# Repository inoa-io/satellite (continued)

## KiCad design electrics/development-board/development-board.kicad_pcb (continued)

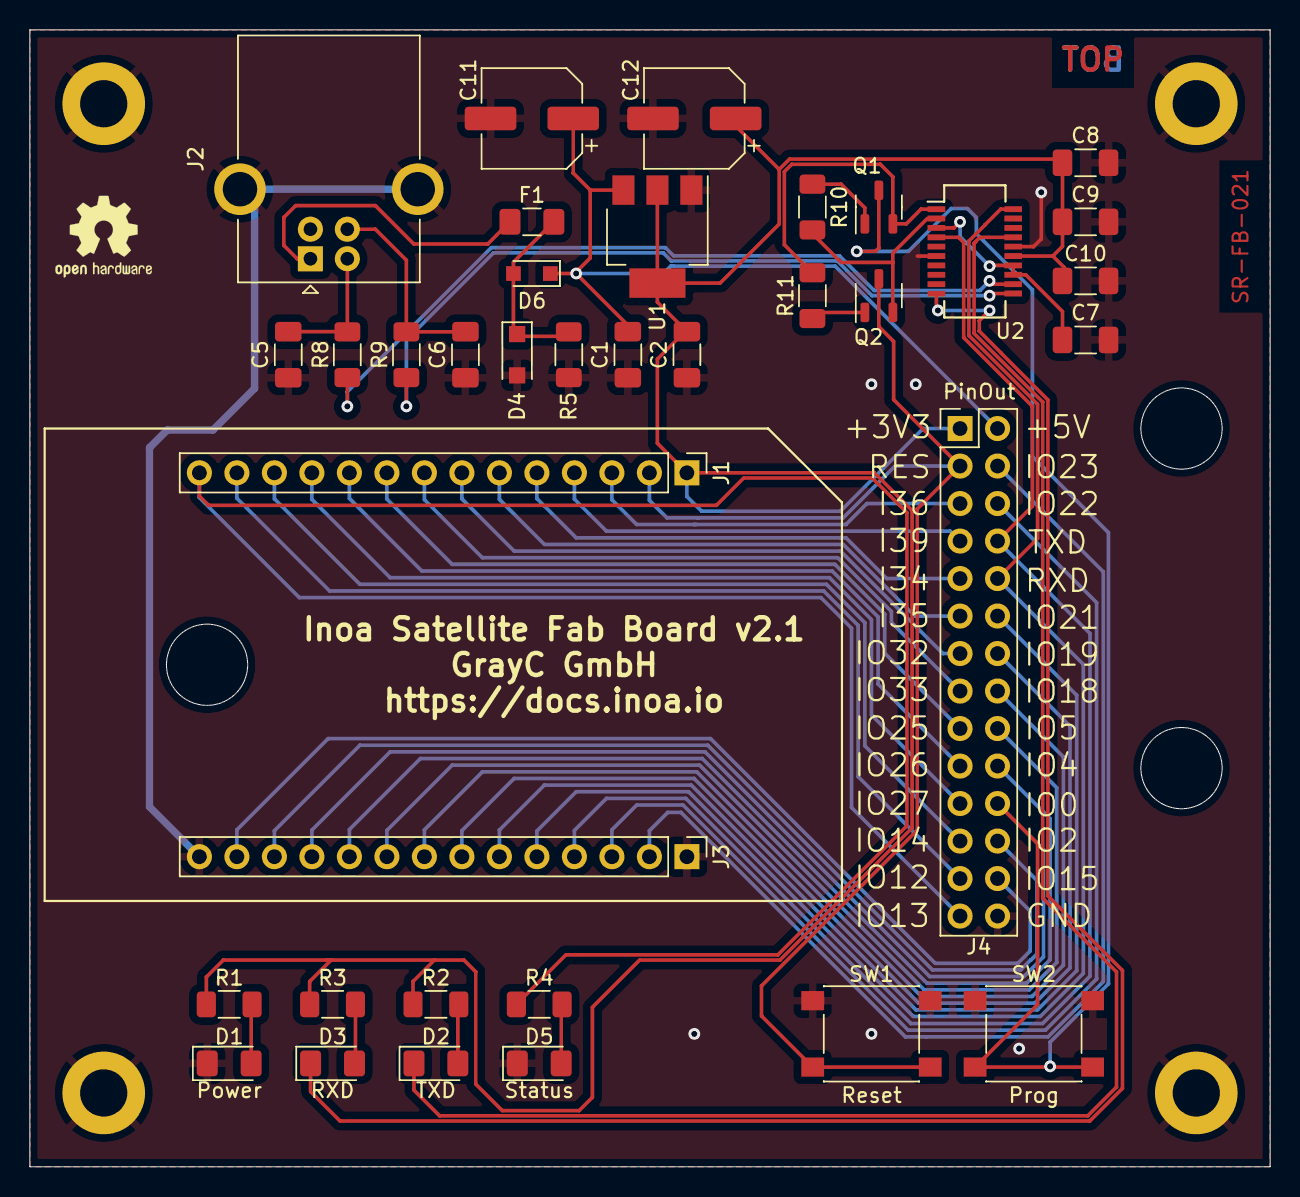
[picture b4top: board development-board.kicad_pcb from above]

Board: 2 copper layers, 84.0 x 77.0 mm, 45 parts (0 on the bottom side), 45 nets.

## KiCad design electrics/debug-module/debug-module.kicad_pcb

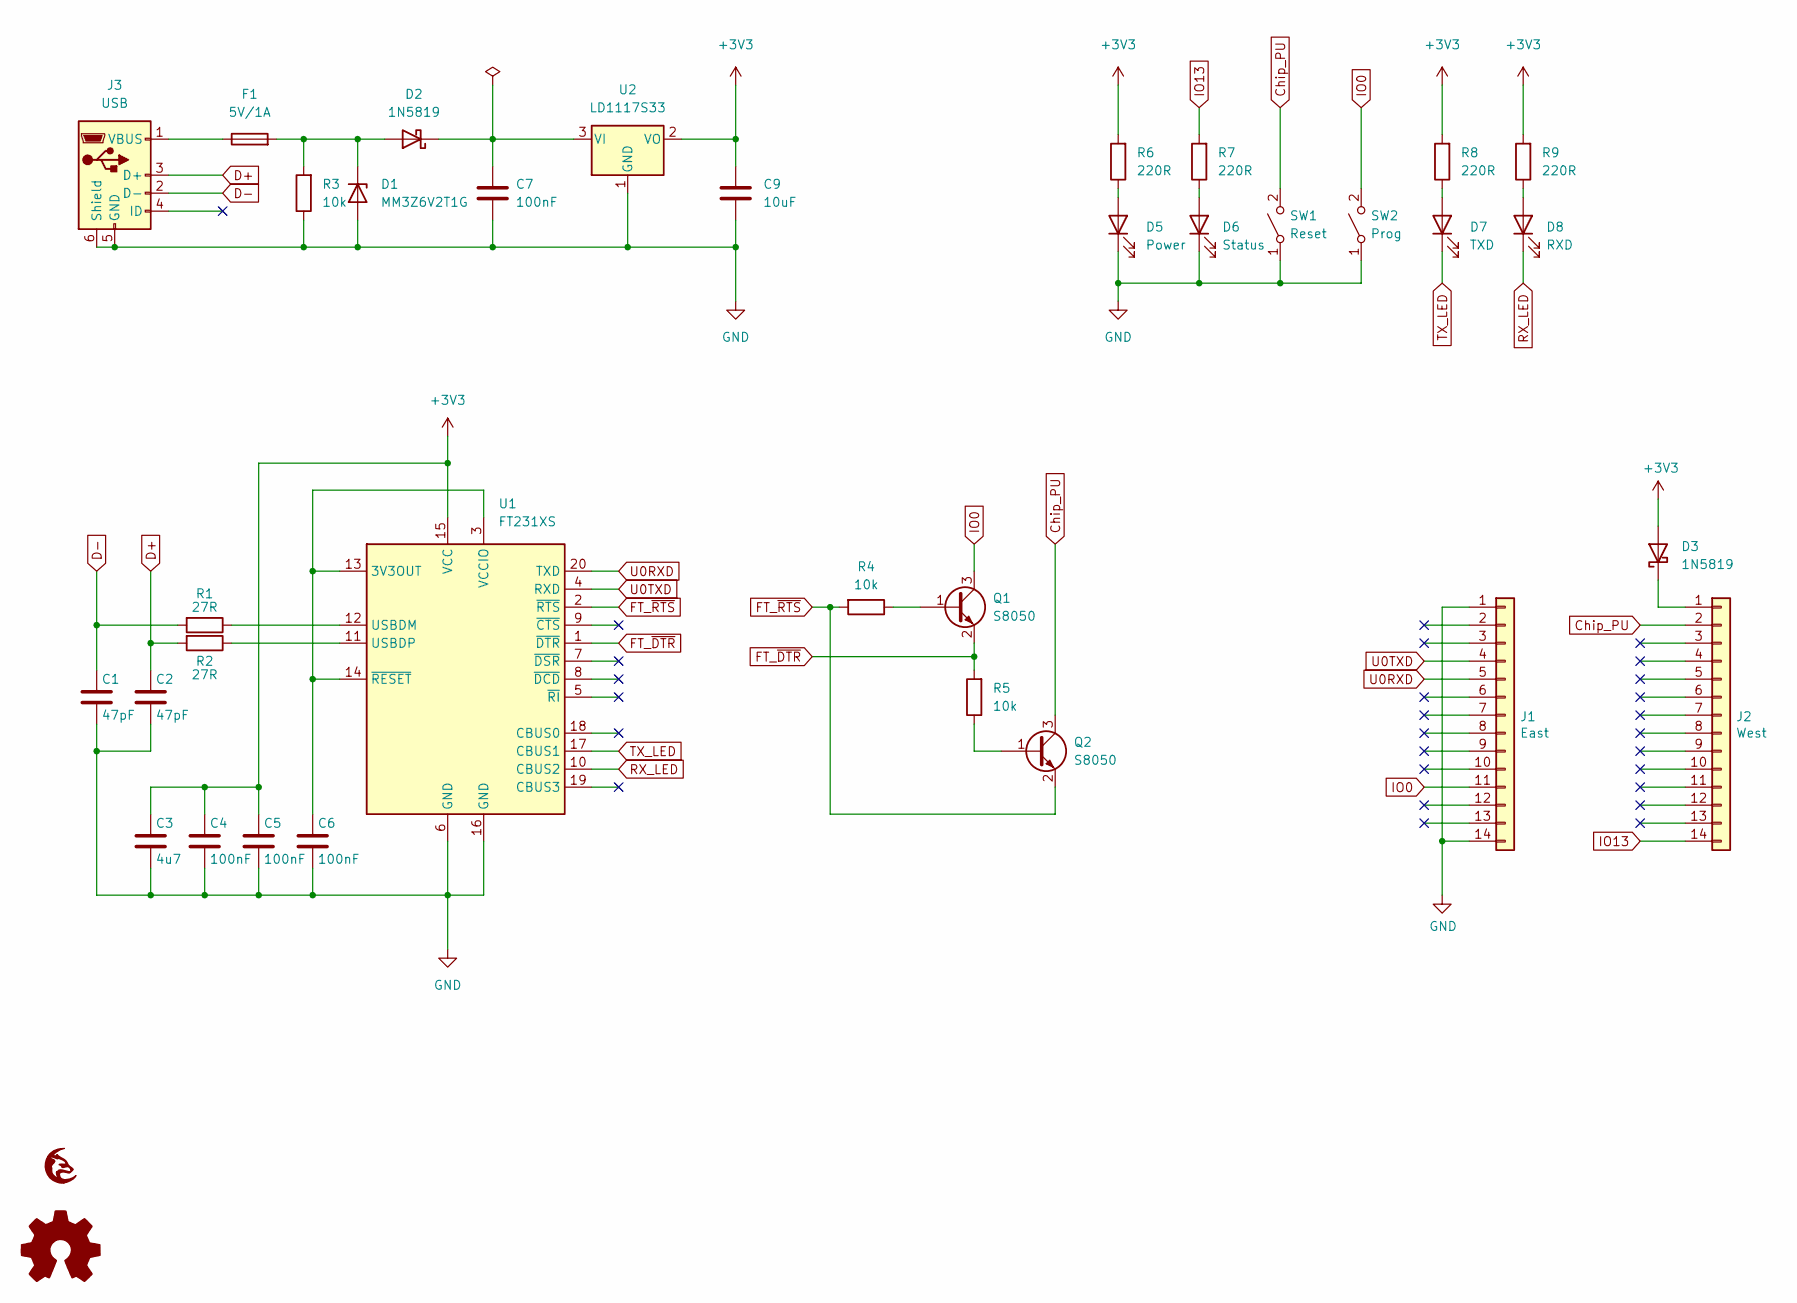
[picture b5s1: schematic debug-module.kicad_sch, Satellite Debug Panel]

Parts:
C1, C2: 47pF; C_1206_3216Metric_Pad1.33x1.80mm_HandSolder
C3: 4u7; C_1206_3216Metric_Pad1.33x1.80mm_HandSolder
C4, C5, C6, C7: 100nF; C_1206_3216Metric_Pad1.33x1.80mm_HandSolder
C9: 10uF; C_1206_3216Metric_Pad1.33x1.80mm_HandSolder
D1: MM3Z6V2T1G; D_SOD-123F
D2, D3: 1N5819; D_SOD-323_HandSoldering
D5: Power; LED_1206_3216Metric_Pad1.42x1.75mm_HandSolder
D6: Status; LED_1206_3216Metric_Pad1.42x1.75mm_HandSolder
D7: TXD; LED_1206_3216Metric_Pad1.42x1.75mm_HandSolder
D8: RXD; LED_1206_3216Metric_Pad1.42x1.75mm_HandSolder
F1: 5V/1A; Fuse_1206_3216Metric_Pad1.42x1.75mm_HandSolder
G1: LOGO; grayc-logo-negative
J1: East; PinSocket_1x14_P2.54mm_Vertical
J2: West; PinSocket_1x14_P2.54mm_Vertical
J3: USB; USB_Micro-B_Wuerth_614105150721_Vertical_CircularHoles
LOGO1: Logo_Open_Hardware_Small; OSHW-Logo_5.7x6mm_SilkScreen
Q1, Q2: S8050; SOT-23-3
R1, R2: 27R; R_1206_3216Metric_Pad1.30x1.75mm_HandSolder
R3, R4, R5: 10k; R_1206_3216Metric_Pad1.30x1.75mm_HandSolder
R6, R7, R8, R9: 220R; R_1206_3216Metric_Pad1.30x1.75mm_HandSolder
SW1: Reset; SW_SPST_PTS645
SW2: Prog; SW_SPST_PTS645
U1: FT231XS; SSOP-20_3.9x8.7mm_P0.635mm
U2: LD1117S33; SOT-223-3_TabPin2

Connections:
+3V3: C3.1, C4.1, C5.1, C9.1, D3.2 (A), R6.2, R8.2, R9.2, U1.15 (VCC), U2.2 (VO)
Chip_PU: J2.2, Q2.3 (C), SW1.2 (B)
D+: C2.1, J3.3 (D+), R2.2
D-: C1.1, J3.2 (D-), R1.2
FT_~DTR: Q1.2 (E), R5.2, U1.1 (~DTR)
FT_~RTS: Q2.2 (E), R4.2, U1.2 (~RTS)
GND: C1.2, C2.2, C3.2, C4.2, C5.2, C6.2, C7.2, C9.2, D1.2 (A), D5.1 (K), D6.1 (K), J1.1, J1.14, J3.5 (GND), J3.6 (Shield), R3.1, SW1.1 (A), SW2.1 (A), U1.6 (GND), U1.16 (GND), U2.1 (GND)
IO0: J1.11, Q1.3 (C), SW2.2 (B)
IO13: J2.14, R7.2
unnamed: C6.1, U1.3 (VCCIO), U1.13 (3V3OUT), U1.14 (~RESET)
unnamed: C7.1, D2.1 (K), U2.3 (VI)
unnamed: D1.1 (K), D2.2 (A), F1.2, R3.2
unnamed: D5.2 (A), R6.1
unnamed: D6.2 (A), R7.1
unnamed: D7.2 (A), R8.1
unnamed: D8.2 (A), R9.1
unnamed: F1.1, J3.1 (VBUS)
unnamed: D3.1 (K), J2.1
unnamed: Q1.1 (B), R4.1
unnamed: Q2.1 (B), R5.1
unnamed: R1.1, U1.12 (USBDM)
unnamed: R2.1, U1.11 (USBDP)
RX_LED: D8.1 (K), U1.10 (CBUS2)
TX_LED: D7.1 (K), U1.17 (CBUS1)
U0RXD: J1.5, U1.20 (TXD)
U0TXD: J1.4, U1.4 (RXD)

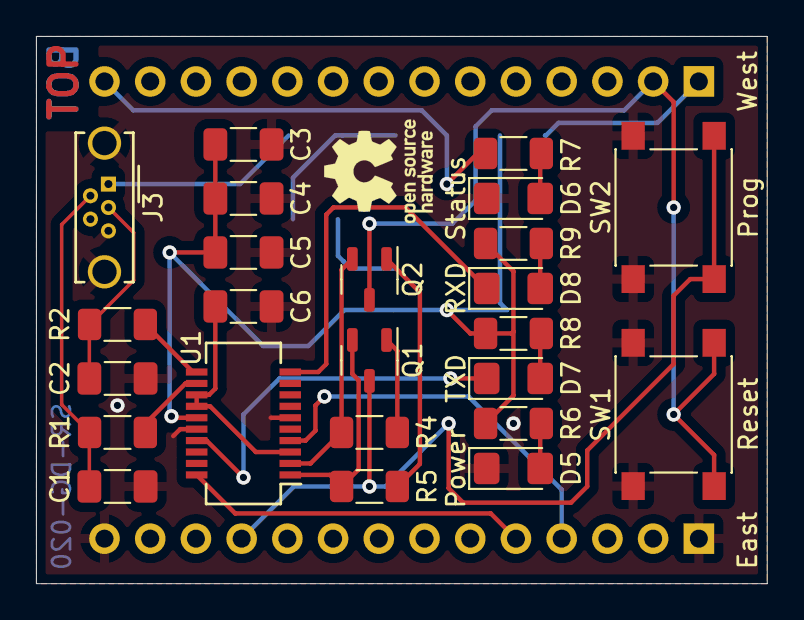
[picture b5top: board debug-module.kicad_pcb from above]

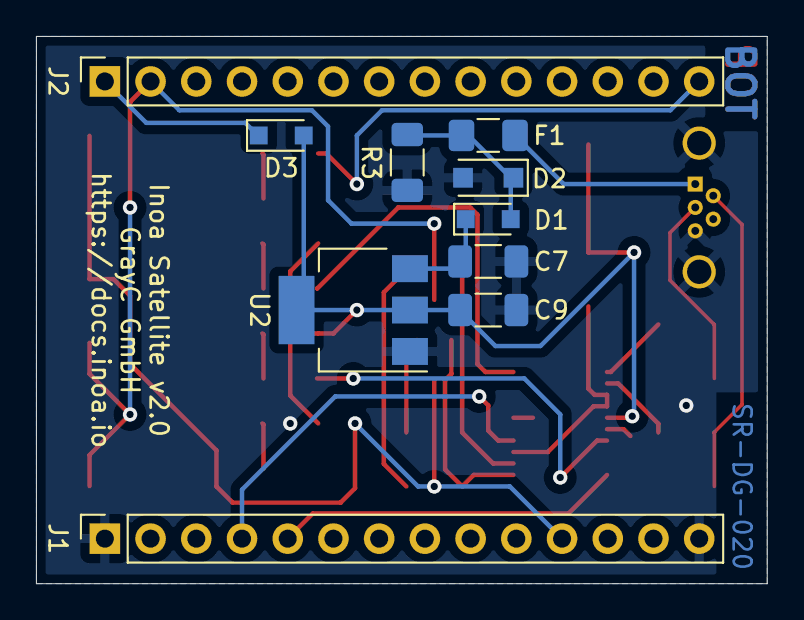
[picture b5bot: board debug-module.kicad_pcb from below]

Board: 2 copper layers, 40.6 x 30.4 mm, 36 parts (11 on the bottom side), 26 nets.

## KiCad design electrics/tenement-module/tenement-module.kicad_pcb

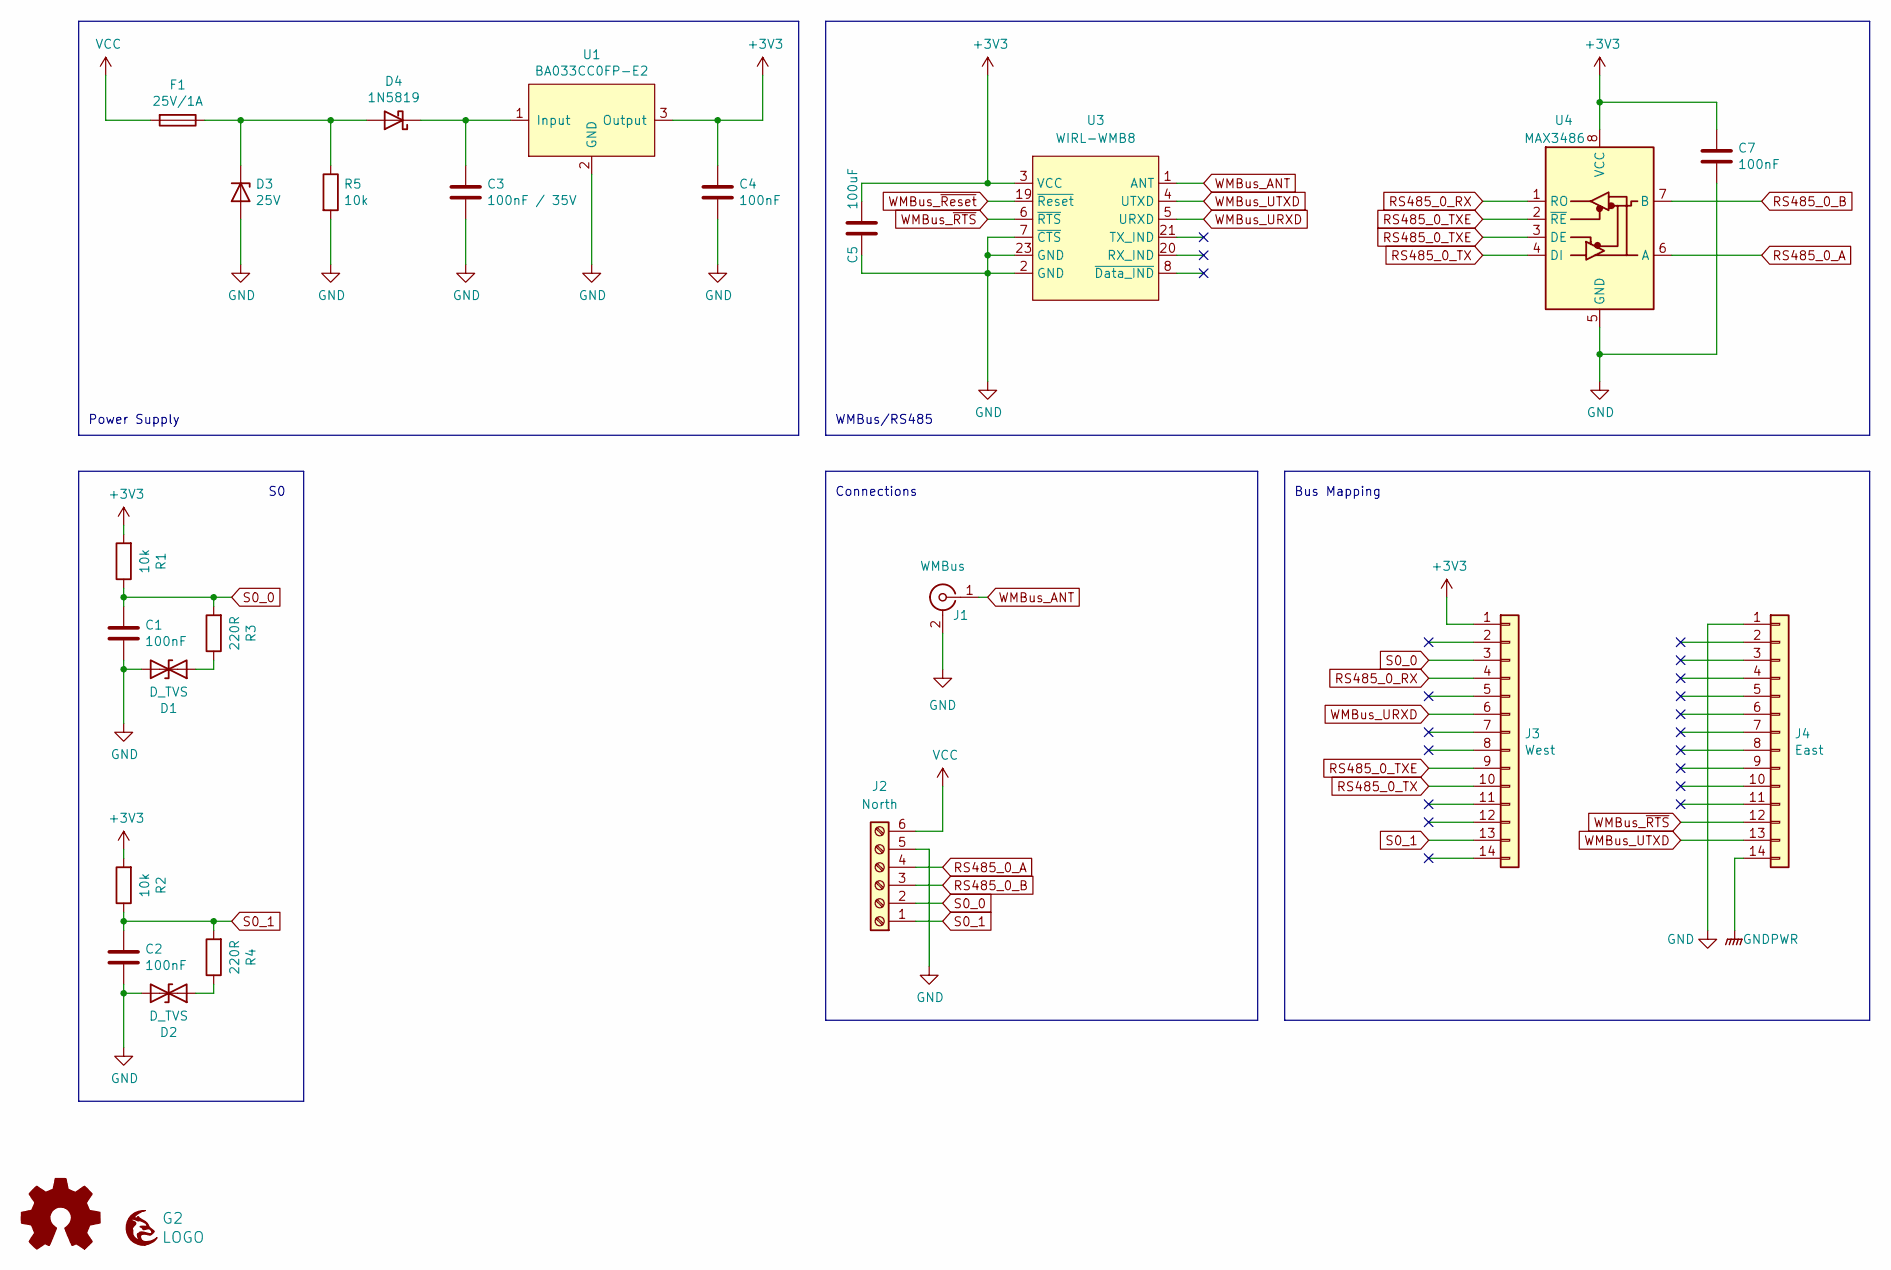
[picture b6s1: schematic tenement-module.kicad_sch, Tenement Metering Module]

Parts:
C1, C2, C4, C7: 100nF; C_1206_3216Metric_Pad1.33x1.80mm_HandSolder
C3: 100nF / 35V; C_1206_3216Metric_Pad1.33x1.80mm_HandSolder
C5: 100uF; C_1206_3216Metric_Pad1.33x1.80mm_HandSolder
D1, D2: D_TVS; D_0603_1608Metric_Pad1.05x0.95mm_HandSolder
D3: 25V; D_SOD-523
D4: 1N5819; D_SOD-323_HandSoldering
F1: 25V/1A; Fuse_1206_3216Metric_Pad1.42x1.75mm_HandSolder
G1: Logo_Open_Hardware_Small; OSHW-Logo2_7.3x6mm_SilkScreen
G2: LOGO; grayc-logo-negative
J1: WMBus; IPEX_20279-001E-01
J2: North; PHOENIX_1935200; mouser# 651-1935200
J3: West; PinHeader_1x14_P2.54mm_Vertical
J4: East; PinHeader_1x14_P2.54mm_Vertical
R1, R2, R5: 10k; R_1206_3216Metric_Pad1.30x1.75mm_HandSolder
R3, R4: 220R; R_1206_3216Metric_Pad1.30x1.75mm_HandSolder
U1: BA033CC0FP-E2; TO-252-3_TabPin2
U3: WIRL-WMB8
U4: MAX3486; SOIC-8_3.9x4.9mm_P1.27mm

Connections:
+3V3: C4.1, C5.1, C7.1, J3.1, R1.2, R2.2, U1.3 (Output), U3.3 (VCC), U4.8 (VCC)
GND: C1.2, C2.2, C3.2, C4.2, C5.2, C7.2, D1.2 (A2), D2.2 (A2), D3.2 (A), J1.2 (Ext), J2.5, J4.1, R5.2, U1.2 (GND), U3.2 (GND), U3.7 (~CTS), U3.23 (GND), U4.5 (GND)
GNDPWR: J4.14
unnamed: C3.1, D4.1 (K), U1.1 (Input)
unnamed: D1.1 (A1), R3.1
unnamed: D2.1 (A1), R4.1
unnamed: D3.1 (K), D4.2 (A), F1.1, R5.1
RS485_0_A: J2.4, U4.6 (A)
RS485_0_B: J2.3, U4.7 (B)
RS485_0_RX: J3.4, U4.1 (RO)
RS485_0_TX: J3.10, U4.4 (DI)
RS485_0_TXE: J3.9, U4.2 (~RE), U4.3 (DE)
S0_0: C1.1, J2.2, J3.3, R1.1, R3.2
S0_1: C2.1, J2.1, J3.13, R2.1, R4.2
VCC: F1.2, J2.6
WMBus_ANT: J1.1 (In), U3.1 (ANT)
WMBus_URXD: J3.6, U3.5 (URXD)
WMBus_UTXD: J4.13, U3.4 (UTXD)
WMBus_~RTS: J4.12, U3.6 (~RTS)
WMBus_~Reset: U3.19 (~Reset)

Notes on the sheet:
WMBus/RS485
Connections
Bus Mapping
Power Supply

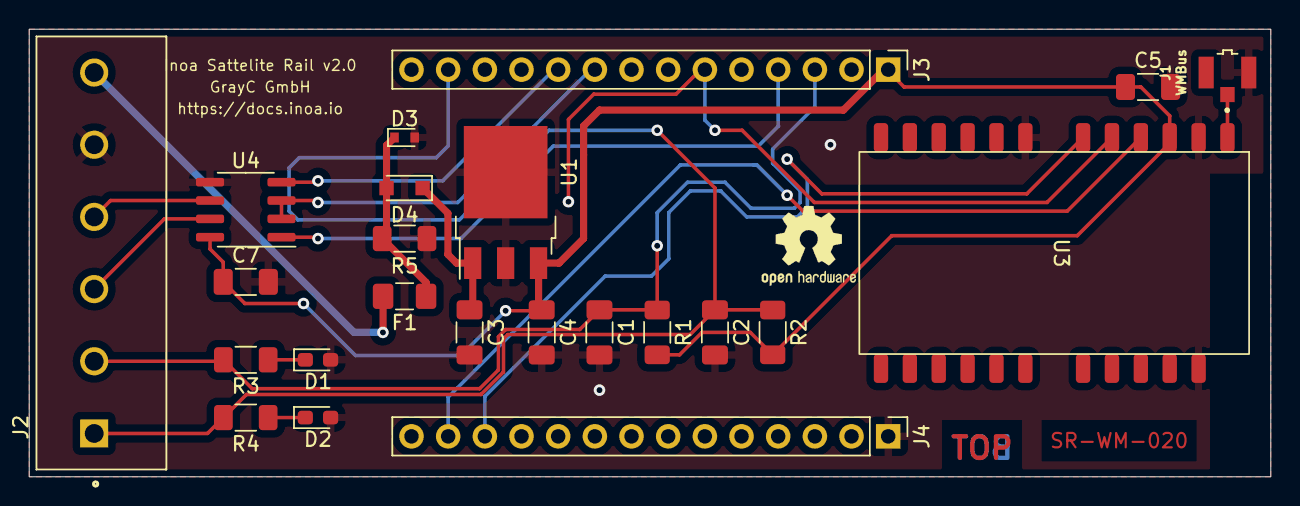
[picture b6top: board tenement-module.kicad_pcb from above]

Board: 2 copper layers, 86.0 x 31.0 mm, 25 parts (1 on the bottom side), 18 nets.

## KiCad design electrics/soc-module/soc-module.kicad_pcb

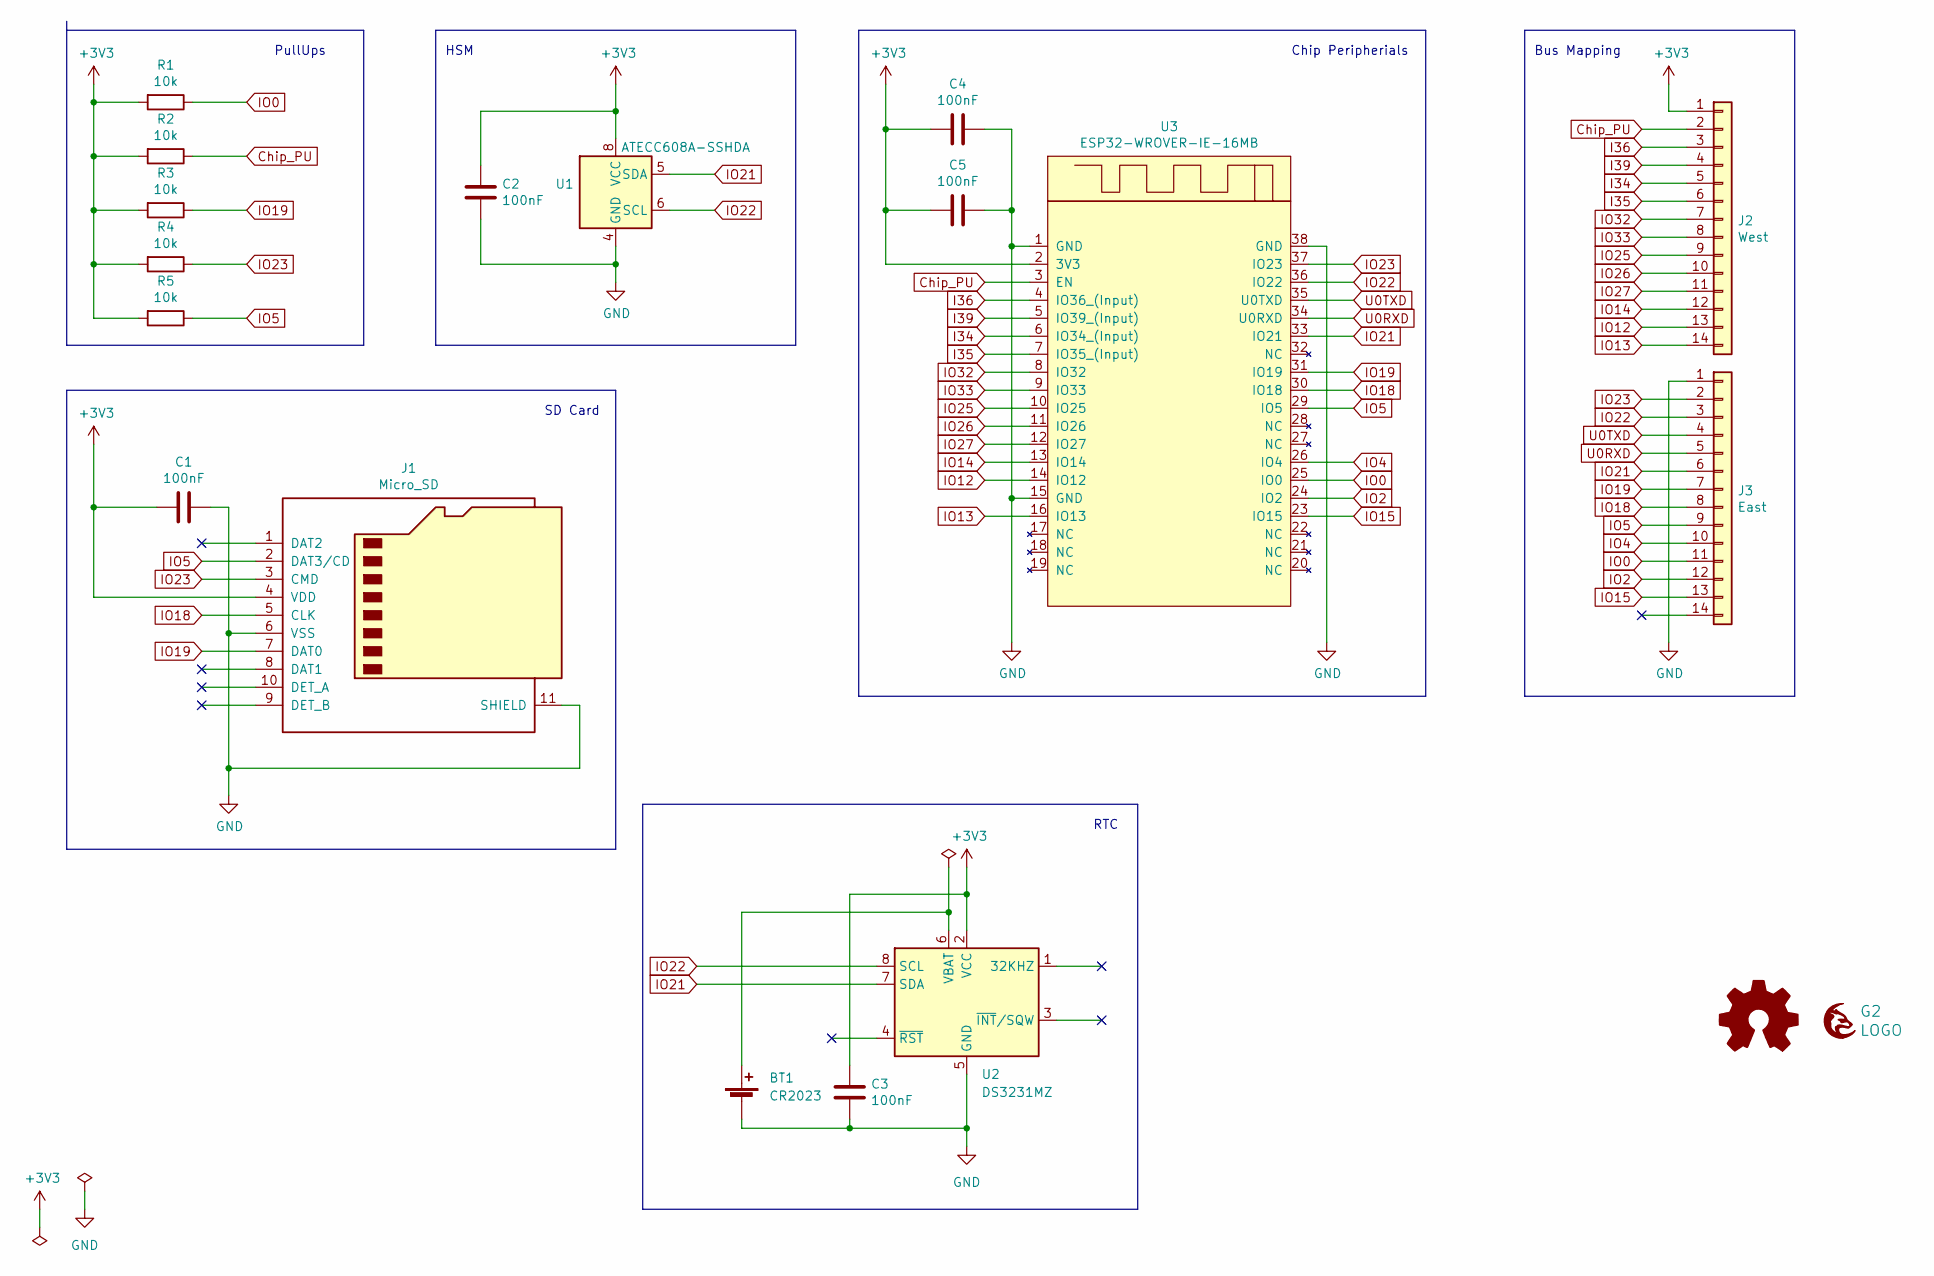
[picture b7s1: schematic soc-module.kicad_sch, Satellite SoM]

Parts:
BT1: CR2023; BatteryHolder_Keystone_1058_1x2032; mouser# 534-1058
C1, C2, C3, C4, C5: 100nF; C_1206_3216Metric_Pad1.33x1.80mm_HandSolder; mouser# 80-C1206C104M5R
G1: Logo_Open_Hardware_Small; OSHW-Logo2_7.3x6mm_SilkScreen
G2: LOGO; grayc-logo-negative
J1: Micro_SD; GCT_MEM2061-01-188-00-A_REVA; mouser# 640-MEM20610118800A
J2: West; PinHeader_1x14_P2.54mm_Vertical; mouser# 437-8018701453001101
J3: East; PinHeader_1x14_P2.54mm_Vertical; mouser# 437-8018701453001101
R1, R2, R3, R4, R5: 10k; R_1206_3216Metric_Pad1.30x1.75mm_HandSolder; mouser# 652-CR0603AFX1002EAS
U1: ATECC608A-SSHDA; SOIC-8_3.9x4.9mm_P1.27mm; mouser# 556-ATECC608ASSHDAB
U2: DS3231MZ; SOIC-8_3.9x4.9mm_P1.27mm; mouser# 700-DS3231MZ+
U3: ESP32-WROVER-IE-16MB; ESP32-WROVER; mouser# 356-ESP32WRVIE2864UC

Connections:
+3V3: C1.2, C2.1, C3.1, C4.2, C5.2, J1.4 (VDD), J2.1, R1.2, R2.2, R3.2, R4.2, R5.2, U1.8 (VCC), U2.2 (VCC), U3.2 (3V3)
Chip_PU: J2.2, R2.1, U3.3 (EN)
GND: BT1.2 (-), C1.1, C2.2, C3.2, C4.1, C5.1, J1.6 (VSS), J1.11 (SHIELD), J3.1, U1.4 (GND), U2.5 (GND), U3.1 (GND), U3.15 (GND), U3.38 (GND)
I34: J2.5, U3.6 (IO34_(Input))
I35: J2.6, U3.7 (IO35_(Input))
I36: J2.3, U3.4 (IO36_(Input))
I39: J2.4, U3.5 (IO39_(Input))
IO0: J3.11, R1.1, U3.25 (IO0)
IO2: J3.12, U3.24 (IO2)
IO4: J3.10, U3.26 (IO4)
IO5: J1.2 (DAT3/CD), J3.9, R5.1, U3.29 (IO5)
IO12: J2.13, U3.14 (IO12)
IO13: J2.14, U3.16 (IO13)
IO14: J2.12, U3.13 (IO14)
IO15: J3.13, U3.23 (IO15)
IO18: J1.5 (CLK), J3.8, U3.30 (IO18)
IO19: J1.7 (DAT0), J3.7, R3.1, U3.31 (IO19)
IO21: J3.6, U1.5 (SDA), U2.7 (SDA), U3.33 (IO21)
IO22: J3.3, U1.6 (SCL), U2.8 (SCL), U3.36 (IO22)
IO23: J1.3 (CMD), J3.2, R4.1, U3.37 (IO23)
IO25: J2.9, U3.10 (IO25)
IO26: J2.10, U3.11 (IO26)
IO27: J2.11, U3.12 (IO27)
IO32: J2.7, U3.8 (IO32)
IO33: J2.8, U3.9 (IO33)
unnamed: BT1.1 (+), U2.6 (VBAT)
U0RXD: J3.5, U3.34 (U0RXD)
U0TXD: J3.4, U3.35 (U0TXD)

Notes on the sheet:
HSM
PullUps
Chip Peripherials
SD Card
RTC
Bus Mapping

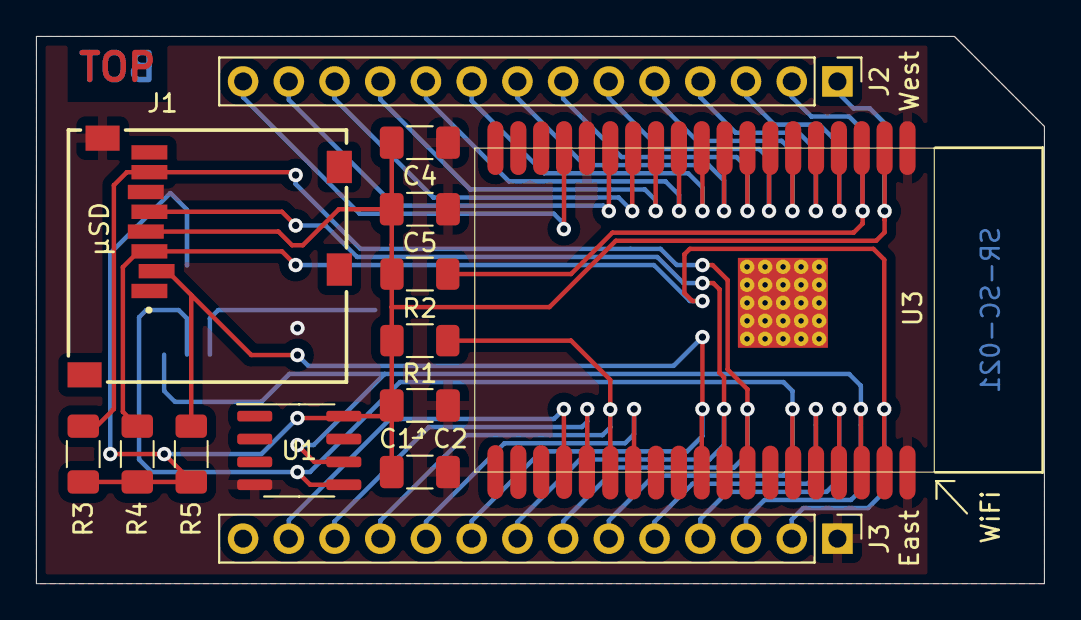
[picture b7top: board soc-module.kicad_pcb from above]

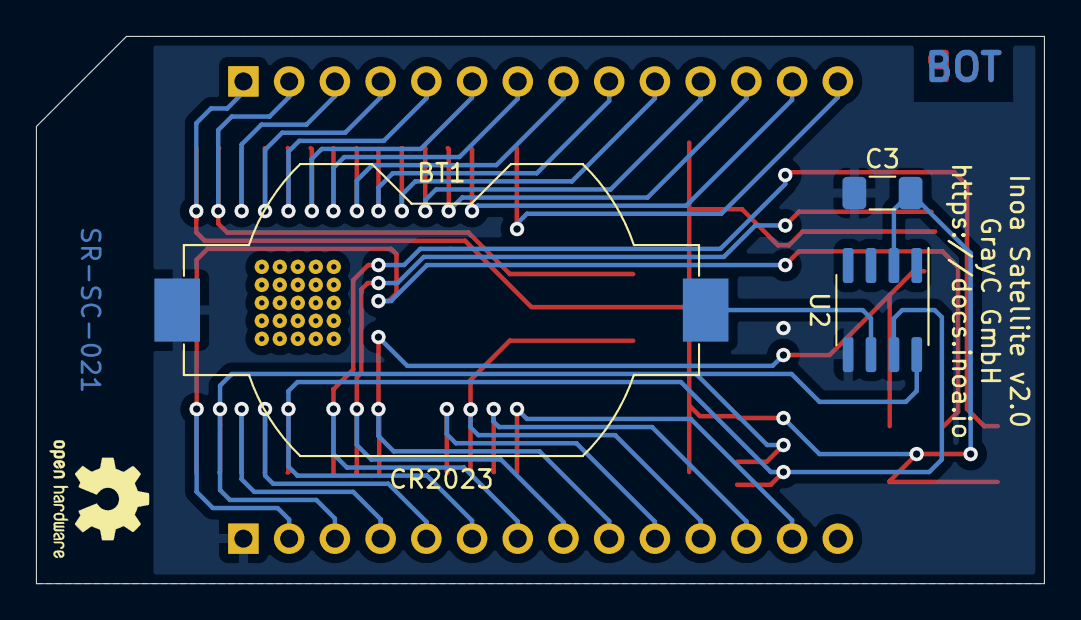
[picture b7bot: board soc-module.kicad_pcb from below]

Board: 2 copper layers, 56.0 x 30.4 mm, 19 parts (5 on the bottom side), 28 nets.

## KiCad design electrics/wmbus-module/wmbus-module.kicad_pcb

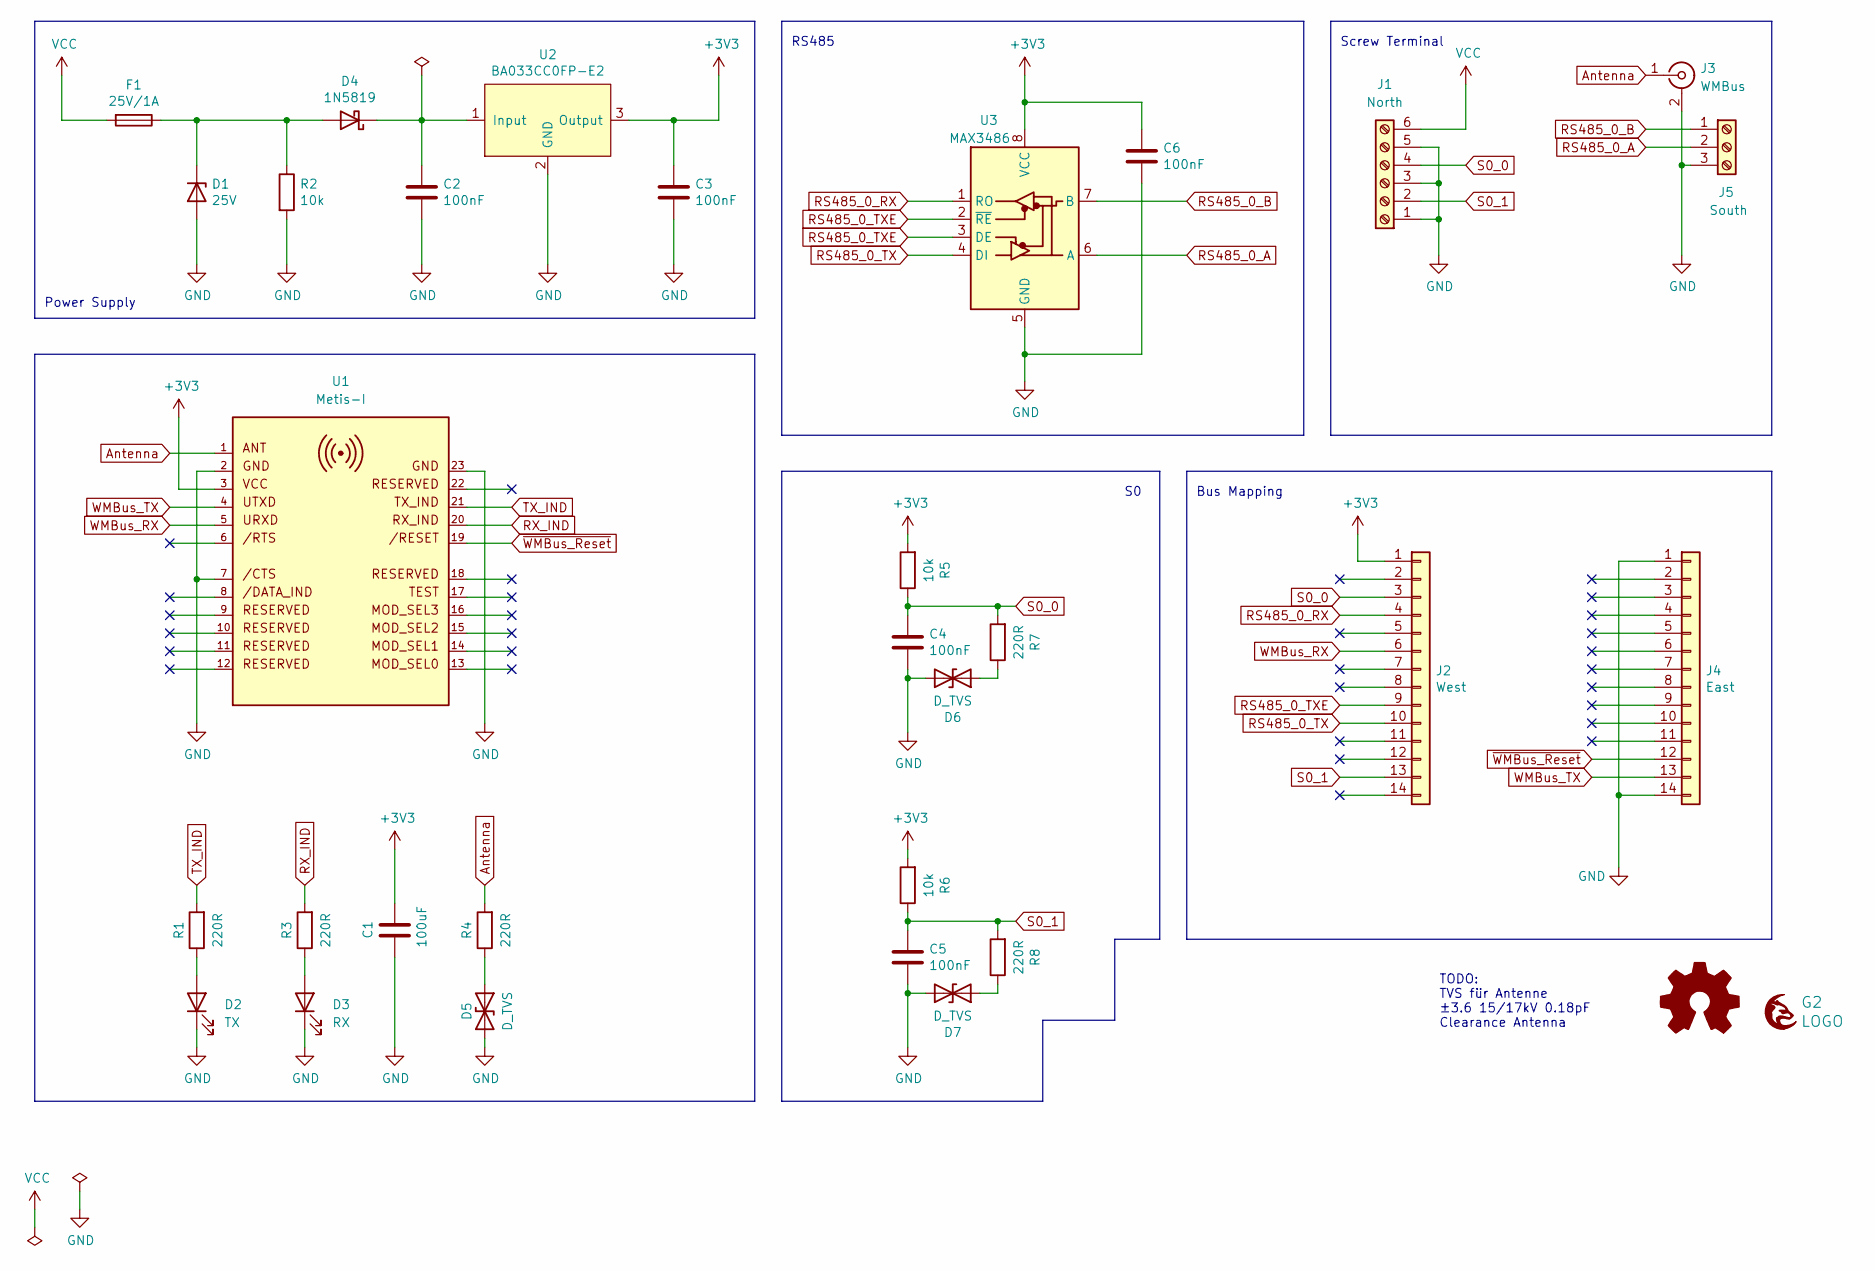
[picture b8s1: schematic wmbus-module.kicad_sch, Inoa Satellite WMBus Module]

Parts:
C1: 100uF; C_1206_3216Metric_Pad1.33x1.80mm_HandSolder
C2, C3, C4, C5, C6: 100nF; C_1206_3216Metric_Pad1.33x1.80mm_HandSolder; mouser# 80-C1206C104M6R
D1: 25V; D_SOD-523; mouser# 750-CPDU24V
D2: TX; LED_1206_3216Metric_Pad1.42x1.75mm_HandSolder; mouser# 696-SML-L1206GCTR
D3: RX; LED_1206_3216Metric_Pad1.42x1.75mm_HandSolder; mouser# 696-SML-L1206GCTR
D4: 1N5819; D_SOD-323_HandSoldering; mouser# 771-PMEG4010CEAX
D5, D6, D7: D_TVS; D_0603_1608Metric_Pad1.05x0.95mm_HandSolder; mouser# 652-CG0603MLC-3.3LE
F1: 25V/1A; Fuse_1206_3216Metric_Pad1.42x1.75mm_HandSolder; mouser# 504-TR/3216FF1-R
G1: Logo_Open_Hardware_Small; OSHW-Logo2_7.3x6mm_SilkScreen
G2: LOGO; grayc-logo-negative
J1: North; PHOENIX_1935200; mouser# 651-1935200
J2: West; PinHeader_1x14_P2.54mm_Vertical; mouser# 855-M20-9991446
J3: WMBus; SMA_Amphenol_901-143_Horizontal
J4: East; PinHeader_1x14_P2.54mm_Vertical; mouser# 855-M20-9991446
J5: South; PHOENIX_1711039
R1, R3, R4, R7, R8: 220R; R_1206_3216Metric_Pad1.30x1.75mm_HandSolder; mouser# 652-CR0603FX-2200ELF
R2, R5, R6: 10k; R_1206_3216Metric_Pad1.30x1.75mm_HandSolder; mouser# 652-CR1206JW-103ELF
U1: Metis-I; WE-FP-1
U2: BA033CC0FP-E2; TO-252-3_TabPin2; mouser# 755-BA033CC0FP-E2
U3: MAX3486; SOIC-8_3.9x4.9mm_P1.27mm; mouser# 700-MAX3486EESA

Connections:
+3V3: C1.1, C3.1, C6.1, J2.1, R5.2, R6.2, U1.3, U2.3 (Output), U3.8 (VCC)
Antenna: J3.1 (In), R4.2, U1.1
GND: C1.2, C2.2, C3.2, C4.2, C5.2, C6.2, D1.2 (A), D2.1 (K), D3.1 (K), D5.2 (A2), D6.2 (A2), D7.2 (A2), J1.1, J1.3, J1.5, J3.2 (Ext), J4.1, J4.14, J5.3, R2.2, U1.2, U1.7, U1.23, U2.2 (GND), U3.5 (GND)
unnamed: C2.1, D4.1 (K), U2.1 (Input)
unnamed: D1.1 (K), D4.2 (A), F1.1, R2.1
unnamed: D2.2 (A), R1.1
unnamed: D3.2 (A), R3.1
unnamed: D5.1 (A1), R4.1
unnamed: D6.1 (A1), R7.1
unnamed: D7.1 (A1), R8.1
RS485_0_A: J5.2, U3.6 (A)
RS485_0_B: J5.1, U3.7 (B)
RS485_0_RX: J2.4, U3.1 (RO)
RS485_0_TX: J2.10, U3.4 (DI)
RS485_0_TXE: J2.9, U3.2 (~RE), U3.3 (DE)
RX_IND: R3.2, U1.20
S0_0: C4.1, J1.4, J2.3, R5.1, R7.2
S0_1: C5.1, J1.2, J2.13, R6.1, R8.2
TX_IND: R1.2, U1.21
VCC: F1.2, J1.6
WMBus_RX: J2.6, U1.5
WMBus_TX: J4.13, U1.4
~WMBus_Reset: J4.12, U1.19

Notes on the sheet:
TODO: TVS für Antenne ±3.6 15/17kV 0.18pF Clearance Antenna
Bus Mapping
RS485
Power Supply
Screw Terminal

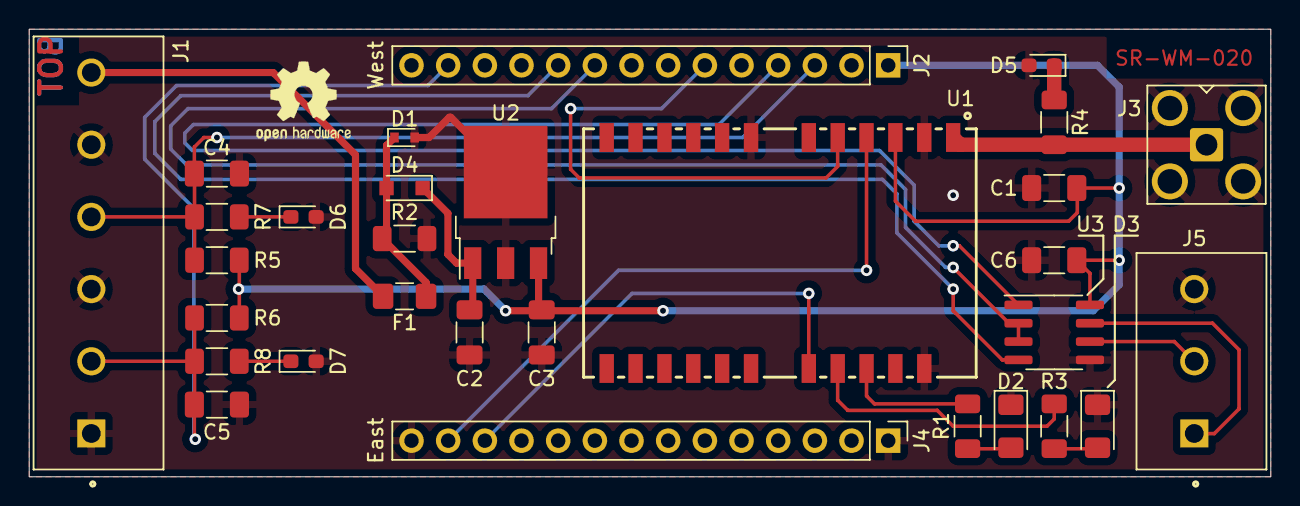
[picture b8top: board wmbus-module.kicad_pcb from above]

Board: 2 copper layers, 86.0 x 31.0 mm, 32 parts (1 on the bottom side), 23 nets.

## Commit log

2021-11-09 Initial Project Structure
2021-11-09 SoC Module Work On
2021-11-24 Ongoing Work Metering Module
2021-11-26 Consolidate subfolders
2021-11-26 Added workflow and build stuff
2021-12-01 Ongoing
2021-12-15 Ongoing Work
2022-01-20 Ongoing Work. Still not ready for small and dedicated commits.
2022-02-01 Added Datasheets and Images
2022-02-01 Review of CI/CD workflows
2022-02-01 Added content to README
2022-02-01 Use a cheaper SD card interface
2022-02-01 Generic build script
2022-02-01 Use a GPIO expander for metering module to safe pins
2022-02-01 Added build badge to README
2022-02-09 Introduce new serial numbering scheme
2022-02-09 Added pin out section to documentation
2022-02-09 Added Satellite image to documentation
2022-03-04 Work on Ethernet module
2022-03-04 Fix build
2022-03-04 Added panel module to CI build
2022-03-08 Added Panel Module to build
2022-03-09 Added dedicated CI KiBot config
2022-03-10 Added metering module to CI build
2022-03-18 Better Silk placings for Panel Module
2022-03-18 Preparation of LoRa Metering Module
2022-03-18 NB IoT ongoing work
2022-03-22 Added SMA connector for LoRa module
2022-03-29 Ongoing work LoRa module
2022-07-05 Added OpenHardware Logo to PCBs
2022-07-05 Fix Footprint of MCP23009
2022-07-20 Fix too low net clearance
2022-12-12 Adjust CI/CD jobs to use KiCad 6
2022-12-12 Migrate panel module project
2022-12-14 Unify KiBot config
2022-12-20 Migrate Ethernet, SoC, Metering Modules to KiCad6
2023-01-02 Change build order to find out more about strange behavior
2023-01-02 Trigger build also on workflow changes
2023-01-02 Try to increase log level to track error
2023-01-16 Switch to KiCad 6 schematic files
2023-01-16 Fix / Ignore Errors in panel module
2023-01-16 Disable cost calculation for now
2023-01-16 Fixing more ERC errors
2023-01-16 Remove outdated files and settings
2023-01-16 Trim further warnings and errors
2023-01-17 Update documentation
2023-01-17 Feature/kicad 6 migration (#1)
    * Adjust CI/CD jobs to use KiCad 6
    * Migrate panel module project
    * Unify KiBot config
    * Migrate Ethernet, SoC, Metering Modules to KiCad6
    * Change build order to find out more about strange behavior
    * Trigger build also on workflow changes
2023-01-19 Migrate in-progress projects
2023-01-19 Feature/kicad 6 migration (#2)
    * Adjust CI/CD jobs to use KiCad 6
    * Migrate panel module project
    * Unify KiBot config
    * Migrate Ethernet, SoC, Metering Modules to KiCad6
    * Change build order to find out more about strange behavior
    * Trigger build also on workflow changes
2023-02-13 Restructured project to get common builds and documentation
2023-02-13 Fix main job yaml
2023-02-13 Feature/kicad 6 migration (#3)
    * Adjust CI/CD jobs to use KiCad 6
    * Migrate panel module project
    * Unify KiBot config
    * Migrate Ethernet, SoC, Metering Modules to KiCad6
    * Change build order to find out more about strange behavior
    * Trigger build also on workflow changes
2023-02-13 Deployed 6ba27ca with MkDocs version: 1.4.2
2023-02-13 Fill docs with minimal information
2023-02-13 Feature/kicad 6 migration (#4)
    * Adjust CI/CD jobs to use KiCad 6
    * Migrate panel module project
    * Unify KiBot config
    * Migrate Ethernet, SoC, Metering Modules to KiCad6
    * Change build order to find out more about strange behavior
    * Trigger build also on workflow changes
2023-02-15 Added more up-to-date images to documentation
2023-02-15 Feature/kicad 6 migration (#5)
    * Adjust CI/CD jobs to use KiCad 6
    * Migrate panel module project
    * Unify KiBot config
    * Migrate Ethernet, SoC, Metering Modules to KiCad6
    * Change build order to find out more about strange behavior
    * Trigger build also on workflow changes
2023-02-15 Improve installation guide
2023-02-17 Feature/kicad 6 migration (#6)
    * Adjust CI/CD jobs to use KiCad 6
    * Migrate panel module project
    * Unify KiBot config
    * Migrate Ethernet, SoC, Metering Modules to KiCad6
    * Change build order to find out more about strange behavior
    * Trigger build also on workflow changes
2023-03-06 Added proper PCB pictures to build output
2023-03-06 Added product numbers for cost calculation
2023-03-06 Feature/kicad 6 migration (#7)
    * Adjust CI/CD jobs to use KiCad 6
    * Migrate panel module project
    * Unify KiBot config
    * Migrate Ethernet, SoC, Metering Modules to KiCad6
    * Change build order to find out more about strange behavior
    * Trigger build also on workflow changes
2023-03-06 Reactivate KiCost
2023-03-10 Feature/kicad 6 migration (#8)
    * Added proper PCB pictures to build output
    * Added product numbers for cost calculation
    * Reactivate KiCost
2023-03-17 Remove outdated files to clean things up
2023-03-17 Added missing part numbers for metering module
2023-03-17 Added 6 position screw terminal
2023-03-17 Added "mieterstrom" module
2023-03-17 Throw generated XML files out of version control
2023-03-17 Add "mieterstrom" module to local build
2023-03-17 Add "Mieterstrom" module to documentation
2023-03-17 Added "Mieterstrom" module to CI/CD
2023-03-17 Feature/dedicated mieterstrom module (#9)
    * Remove outdated files to clean things up
    * Added missing part numbers for metering module
    * Added 6 position screw terminal
    * Added "mieterstrom" module
    * Throw generated XML files out of version control
    * Add "mieterstrom" module to local build
2023-04-03 Added optional RTC to SoC module
2023-04-03 Feature/rtc for soc module (#10)
    * Remove outdated files to clean things up
    * Added missing part numbers for metering module
    * Added 6 position screw terminal
    * Added "mieterstrom" module
    * Throw generated XML files out of version control
    * Add "mieterstrom" module to local build
2023-10-10 Add tenant metering module to documentation
2023-10-10 Add tenant metering module to documentation (#11)
2023-10-12 Fix wrong resistor manufacturer number in panel module
2023-10-12 Added missing labels for bus connectors in "Mieterstrom" module
2023-10-12 Added missing 3D model for BC66NB
2023-10-12 Finalized PoC for M-Bus module
2023-10-12 Updated documentation
2023-10-12 M bus module (#12)
    * Fix wrong resistor manufacturer number in panel module
    * Added missing labels for bus connectors in "Mieterstrom" module
    * Added missing 3D model for BC66NB
    * Finalized PoC for M-Bus module
    * Updated documentation
2023-10-19 Added markdown linter
2023-10-19 Fixed typos and missing resources
2023-10-19 Changed License to CERN-OHL-P
2023-10-19 Opensource (#13)
    * Added markdown linter
    * Fixed typos and missing resources
    * Changed License to CERN-OHL-P
2024-03-06 Remove "In Progress" stuff
2024-03-19 Fix all ERC and DRC warnings during build
2024-11-27 Add CT metering module
2024-11-27 Review Fixes
2024-11-28 Fix missing 3D image
2024-11-28 Add CT metering module (#14)
    * Add CT metering module
    * Review Fixes
    * Fix missing 3D image
    ---------
2025-01-07 INOA-372 Finalize CT module
2025-01-07 INOA-372 Fix out of stock components in SoC module
2025-01-07 INOA-372 Fix out of stock components in TM module
2025-01-07 INOA-372 Rename Fab and Dev board
2025-01-07 INOA-372 Fix autoprogrammer for debug module
2025-01-07 INOA-372 Fix schematic annotations for MBus module
2025-01-07 INOA-372 Enhance documentation
2025-01-07 INOA-372 Add new modules to build pipeline
2025-01-07 INOA-372 EMS, Debug, Development module (#15)
    * Add CT metering module
    * Review Fixes
    * Fix missing 3D image
    * INOA-372 Finalize CT module
    * INOA-372 Fix out of stock components in SoC module
    * INOA-372 Fix out of stock components in TM module
2026-03-18 INOA-372 Add LTE module
